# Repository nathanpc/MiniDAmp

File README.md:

# MiniDAmp

A low-distortion (<0.05% THD @ 1kHz) 44W (22W per channel) class AB power amplifier.

## THD

This is the THD graph of the amplifier at full power into a 8 ohm load made using [plot_thd.py](https://gist.github.com/nathanpc/464b65f48d494179be13):

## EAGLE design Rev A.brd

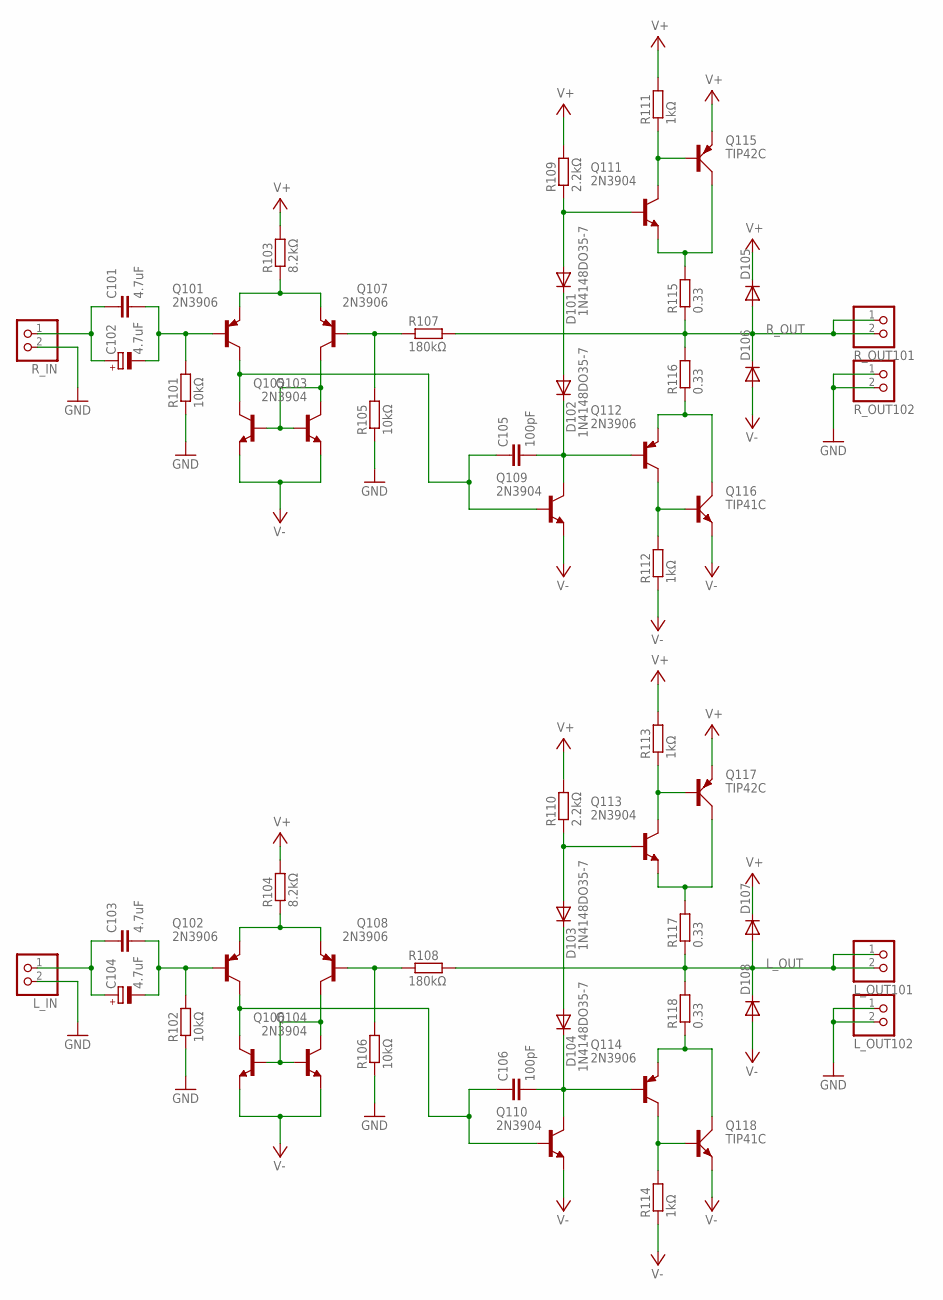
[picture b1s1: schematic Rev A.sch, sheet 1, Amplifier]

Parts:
C101, C103: 4.7uF; C225-113X268
C102, C104: 4.7uF; E2-5
C105, C106: 100pF; C050-050X075
D101, D102, D103, D104, D105, D106, D107, D108: 1N4148DO35-7; DO35-7
L_IN: JST_2PIN-THM; JST-PH-2-THM
L_OUT101, L_OUT102: JST_2PIN-THM; JST-PH-2-THM
Q101, Q102, Q107, Q108, Q112, Q114: 2N3906; TO92
Q103, Q104, Q105, Q106, Q109, Q110, Q111, Q113: 2N3904; TO92
Q115, Q117: TIP42C; TO220AV
Q116, Q118: TIP41C; TO220AV
R101, R102, R105, R106: 10kΩ; 0207/10
R103, R104: 8.2kΩ; 0207/10
R107, R108: 180kΩ; 0207/10
R109, R110: 2.2kΩ; 0207/10
R111, R112, R113, R114: 1kΩ; 0207/10
R115, R116, R117, R118: 0.33; 0414/15
R_IN: JST_2PIN-THM; JST-PH-2-THM
R_OUT101, R_OUT102: JST_2PIN-THM; JST-PH-2-THM

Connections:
GND: L_IN.2 (1), L_OUT102.1 (2), L_OUT102.2 (1), R101.1, R102.1, R105.1, R106.1, R_IN.2 (1), R_OUT102.1 (2), R_OUT102.2 (1); also elsewhere on the board
L_OUT: D107.A, D108.C, L_OUT101.1 (2), L_OUT101.2 (1), R108.2, R117.1, R118.2
unnamed: D101.A, Q111.2 (B), R109.1
unnamed: Q101.3 (E), Q107.3 (E), R103.1
unnamed: Q103.2 (B), Q105.1 (C), Q105.2 (B), Q107.1 (C)
unnamed: Q104.2 (B), Q106.1 (C), Q106.2 (B), Q108.1 (C)
unnamed: C101.2, C102.-, Q101.2 (B), R101.2
unnamed: C101.1, C102.+, R_IN.1 (2)
unnamed: C105.1, Q101.1 (C), Q103.1 (C), Q109.2 (B)
unnamed: D101.C, D102.A
unnamed: C103.2, C104.-, Q102.2 (B), R102.2
unnamed: Q111.1 (C), Q115.B, R111.1
unnamed: Q112.1 (C), Q116.B, R112.2
unnamed: Q112.3 (E), Q116.C, R116.1
unnamed: Q111.3 (E), Q115.C, R115.2
unnamed: C103.1, C104.+, L_IN.1 (2)
unnamed: C105.2, D102.C, Q109.1 (C), Q112.2 (B)
unnamed: Q107.2 (B), R105.2, R107.1
unnamed: Q102.3 (E), Q108.3 (E), R104.1
unnamed: C106.1, Q102.1 (C), Q104.1 (C), Q110.2 (B)
unnamed: D103.C, D104.A
unnamed: D103.A, Q113.2 (B), R110.1
unnamed: Q113.1 (C), Q117.B, R113.1
unnamed: Q113.3 (E), Q117.C, R117.2
unnamed: Q114.1 (C), Q118.B, R114.2
unnamed: Q114.3 (E), Q118.C, R118.1
unnamed: C106.2, D104.C, Q110.1 (C), Q114.2 (B)
unnamed: Q108.2 (B), R106.2, R108.1
R_OUT: D105.A, D106.C, R107.2, R115.1, R116.2, R_OUT101.1 (2), R_OUT101.2 (1)
V+: D105.C, D107.C, Q115.E, Q117.E, R103.2, R104.2, R109.2, R110.2, R111.2, R113.2; also elsewhere on the board
V-: D106.A, D108.A, Q103.3 (E), Q104.3 (E), Q105.3 (E), Q106.3 (E), Q109.3 (E), Q110.3 (E), Q116.E, Q118.E, R112.1, R114.1; also elsewhere on the board

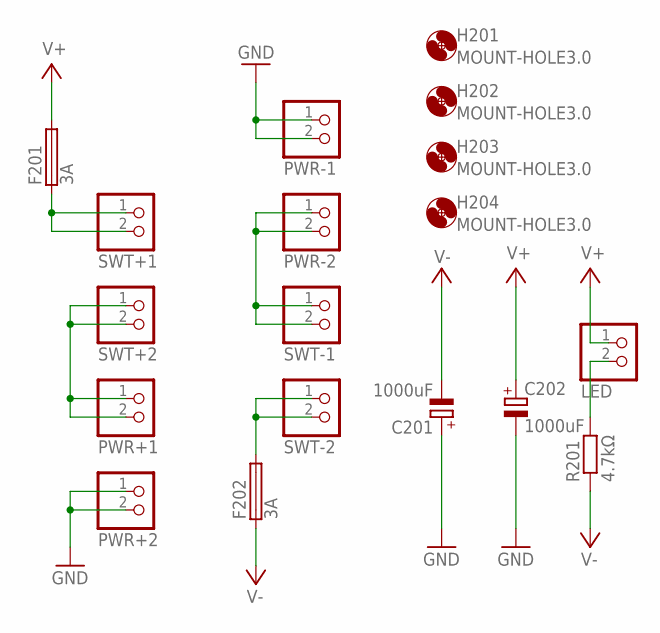
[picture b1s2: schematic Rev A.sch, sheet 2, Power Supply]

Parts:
C201, C202: 1000uF; E5-10,5
F201, F202: 3A; SH22,5
H201, H202, H203, H204: MOUNT-HOLE3.0; 3,0
LED: JST_2PIN-THM; JST-PH-2-THM
PWR+1, PWR+2: JST_2PIN-THM; JST-PH-2-THM
PWR-1, PWR-2: JST_2PIN-THM; JST-PH-2-THM
R201: 4.7kΩ; 0207/10
SWT+1, SWT+2: JST_2PIN-THM; JST-PH-2-THM
SWT-1, SWT-2: JST_2PIN-THM; JST-PH-2-THM

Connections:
GND: C201.+, C202.-, PWR+2.1 (2), PWR+2.2 (1), PWR-1.1 (2), PWR-1.2 (1); also elsewhere on the board
unnamed: LED.2 (1), R201.2
unnamed: PWR+1.1 (2), PWR+1.2 (1), SWT+2.1 (2), SWT+2.2 (1)
unnamed: PWR-2.1 (2), PWR-2.2 (1), SWT-1.1 (2), SWT-1.2 (1)
unnamed: F202.2, SWT-2.1 (2), SWT-2.2 (1)
unnamed: F201.1, SWT+1.1 (2), SWT+1.2 (1)
V+: C202.+, F201.2, LED.1 (2); also elsewhere on the board
V-: C201.-, F202.1, R201.1; also elsewhere on the board

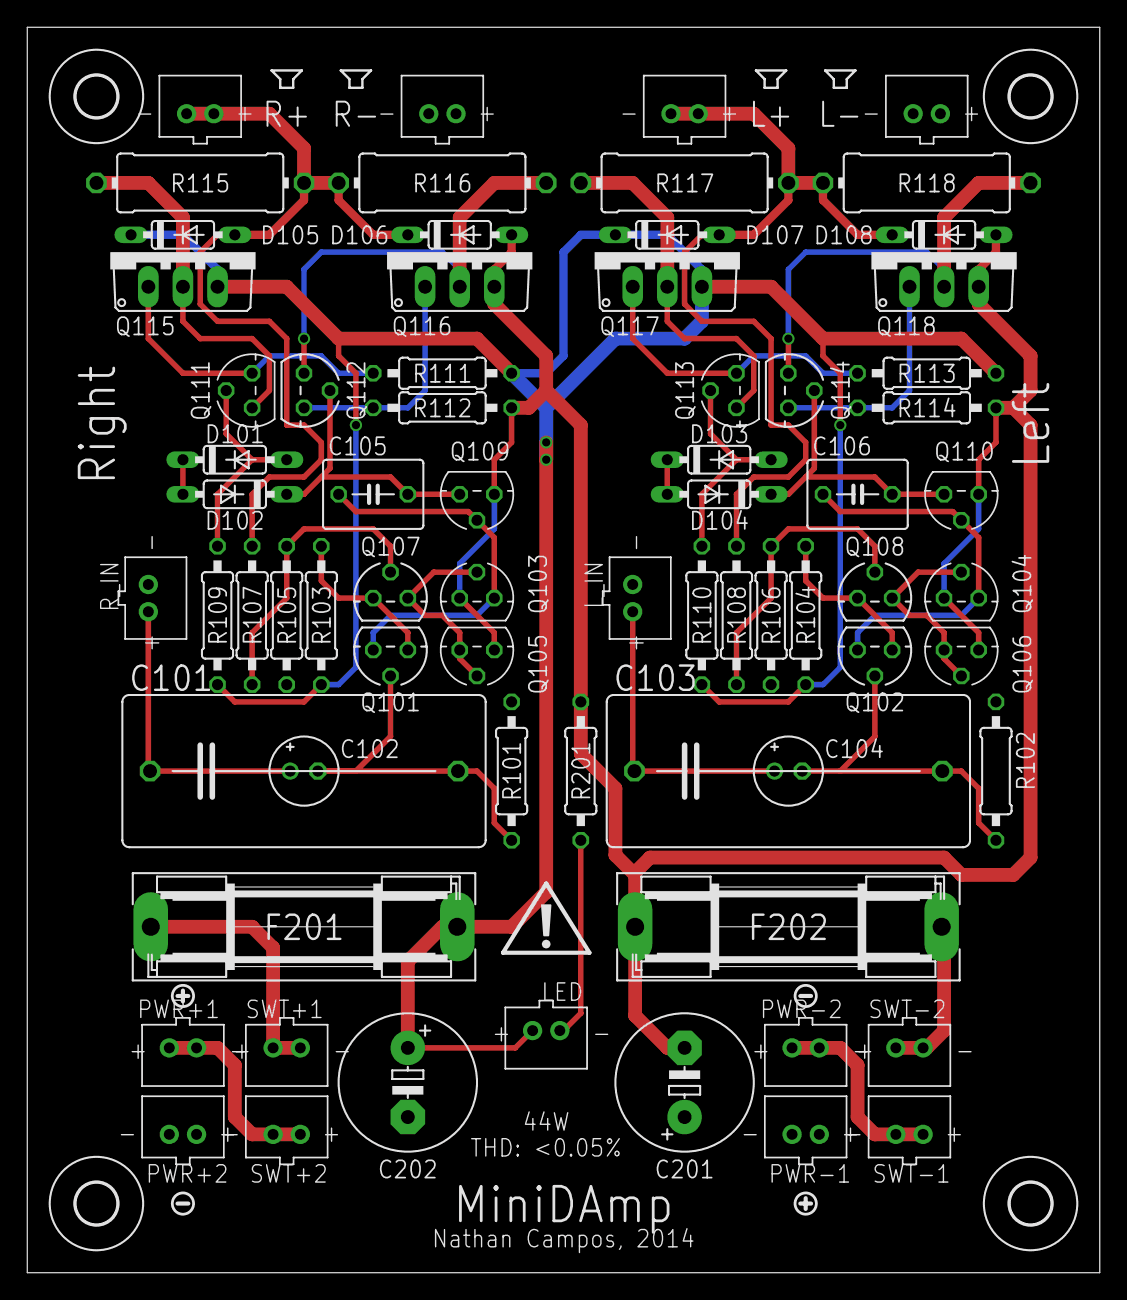
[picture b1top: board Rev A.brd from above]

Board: 4 copper layers, 78.7 x 91.4 mm, 83 parts (0 on the bottom side), 36 nets.

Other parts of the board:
U$1: ICON_EXL-S
U$2, U$3: ICON_MINUS
U$4, U$5: ICON_PLUS
U$6, U$7, U$8, U$9: ICON_SPEAKER

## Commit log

2014-08-10 Added renumbering files to the .gitignore
2014-08-10 Finished the schematic
2014-08-10 Added a title to each sheet
2014-08-10 Renumbering
2014-08-10 Fixed the reversed JST connectors
2014-08-10 Made some changes to the connector arrangement in the power supply
2014-08-10 Removed one LED
2014-08-10 Made major changes to the schematic
2014-08-10 Final changes
2014-08-10 Finished the PCB layout
2014-08-10 Exported the schematic and board layout
2014-08-10 Added some images to the README
2014-08-10 Ready for production
2014-08-10 Updated the THD graph
2014-08-10 Create gh-pages branch via GitHub

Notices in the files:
parts and their libraries:
dicons: Copyright (C) 2004, Bob Starr (rtzaudio@mindspring.com)
